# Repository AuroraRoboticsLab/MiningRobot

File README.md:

# UAF Robot Control Architecture, 2023 Version
## Codebase
The autonomy/ directory contains our robot control stack, written in C++ for Linux and running happily on x86 and ARM based robots including the Raspberry Pi or NVIDIA Jetson.  See [the README in that directory](https://github.com/AuroraRoboticsLab/MiningRobot/blob/master/autonomy/README.txt) for build directions.

## LUNATIC
The "Logically UNcoupled Architecture Technology for Intra-robot Communication" or LUNATIC (pronounced lun-AT-ic, like automatic) is our robot control system, built as a loosely coupled set of microservices.

Using microservices means you can compile, run, and test a single service independently, unlike our previous single monolithic executable the [backend](autonomy/backend/main.cpp).  

Due to the nature of a robotics control stack, being able to efficiently exchange quickly changing data between modules is crucial. We do this using the new MMAP-based shared file data exchange system, the details of which can be found in the [data_exchange.h](autonomy/include/aurora/data_exchange.h) header. 

The data being exchanged is listed in the [lunatic.h](autonomy/include/aurora/lunatic.h) header for the microservices, and [nanoslot_exchange.h](autonomy/nanoslot/include/nanoslot/nanoslot_exchange.h) for the Arduino data.

## Control Software Stack
A basic manual control setup has autonomy/frontend running on the "pilot" machine, and sending commands to the autonomy/backend running onboard the robot.  These commands are sent via UDP broadcast, so they should work anywhere on the same subnet.  The backend talks to the Arduinos directly via USB--each Arduino has a "nanoslot ID" that lets nanoboot connect the appropriate slot program to communicate with it.  To control the robot, all you need is a backend and the slot programs: put the backend into "backend driver" state, and use WASD to drive the robot.

For autonomous robot operations, we rely on a huge variety of microservices, such as the localizer (where is the robot?), path planner (how do we get to the target?), andretti (how do we drive along the path?), vision (what obstacles can we see?), and several other debug tools.

This architecture has been incrementally built up since 2013 by a variety of UAF students for the NASA Robotic Mining Contest.  Unless otherwise noted, everything here is public domain. 

For details on how build and run this software, see autonomy/README.
Send a pull request or email lawlor@alaska.edu if you have comments or suggestions!

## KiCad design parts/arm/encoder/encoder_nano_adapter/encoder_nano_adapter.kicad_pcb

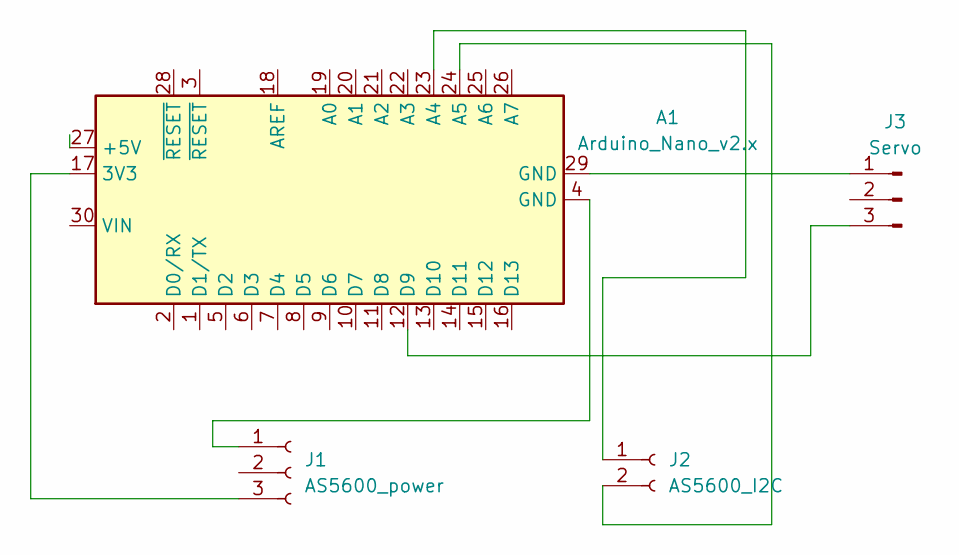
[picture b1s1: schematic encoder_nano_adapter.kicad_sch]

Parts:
A1: Arduino_Nano_v2.x; Arduino_Nano
J1: AS5600_power; PinSocket_1x03_P2.54mm_Vertical
J2: AS5600_I2C; PinSocket_1x02_P2.54mm_Vertical
J3: Servo; PinHeader_1x03_P2.54mm_Vertical

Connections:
unnamed: A1.17 (3V3), J1.3
unnamed: A1.23 (A4), J2.1
unnamed: A1.24 (A5), J2.2
unnamed: A1.12 (D9), J3.3
unnamed: A1.4 (GND), J1.1
unnamed: A1.29 (GND), J3.1

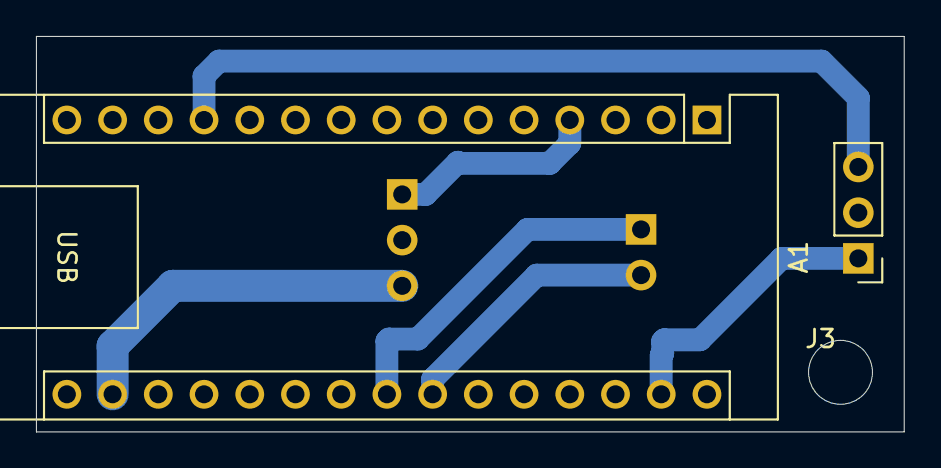
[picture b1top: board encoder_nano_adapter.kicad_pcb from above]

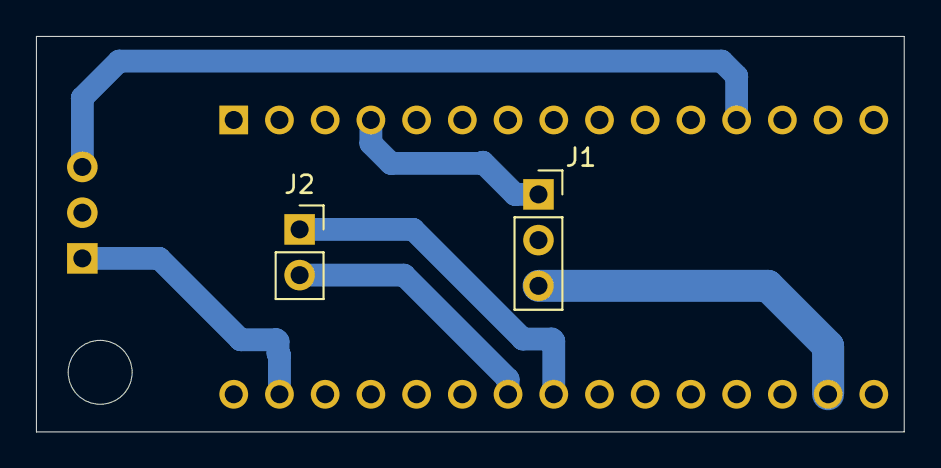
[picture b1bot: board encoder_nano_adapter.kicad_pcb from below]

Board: 2 copper layers, 48.2 x 22.0 mm, 4 parts (2 on the bottom side), 6 nets.

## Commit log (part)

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2023-12-15 Added "--tabletop" vision option, to show simple demo of depth camera processing without a full robot running.
2024-02-22 Moved collision detection constants/functions to excahaul_collision.h
2024-07-29 Swap front scoop controls to match heavy equipment, and sim.
2024-07-29 Don't stop robot because a hazard is detected (e.g., false positive with no tool attached)
2024-09-06 Initial "LawlorBus" test code. Basically like I2C, but instead of pull-up resistors, uses hard I/O pin levels. Designed for direct no-transceiver comms between microcontrollers. Limited to fixed-size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
2024-09-09 Initial 3D printable prototype flat truss.
2024-09-12 Added L truss, with diagonals.
2024-09-23 Add fully 3D printable full-size truss--most vertexes have been printed and tested OK.
2024-09-26 Origami-style truss. Print flat and fold up, to understand geometry.
2024-09-26 Final as-built rev2 trusses, including CAM template for stainless steel endplates.
2024-10-06 These parts used to test geometry of origami truss, mixed results...
2024-10-09 Small demo model of unfolding truss, basically designed as an L truss that can be shipped pre-assembled to the previous truss.
2024-10-28 Initial checkin of a possible robot arm's stepped planetary reducer gear (100:1 reduction ratio).
2024-12-12 3D printed prototype proof of concept works, but needs at least one more revision.
2024-12-13 Significant rework to increase gear reduction ratio (currently 1300:1!) and better constrain motions. Work in progress, hasn't even been test printed.
2024-12-15 Initial ROS2 MoveIt integration for lunatic data exchange and Excahauler robot. Work in progress!
2024-12-18 Version v3C, printed and fully operational! Still needs covers, and could probably be simplified.
2024-12-18 v3F: minor updates to allow multiple motor orientations, guide in bearing screws, tighten up ring bearing clearances.
2025-02-10 Working v4 arm actuator. This "lipless" design works, but wears the sun gear under load, so I think I need to switch back to the retaining bearings.
2025-02-10 Restored planetary bearing lips. About to double the gear reduction, with 4 unique planets.
2025-02-11 v6 actuator design: over 2500:1 total gear reduction, with numbered planets.
2025-02-12 Added "stick" to manually drive sun gear using a cordless drill. It works!
2025-02-17 Version 6, with wire guide tube. Next step is encoder sensor bracket / gear cover.
2025-02-19 Add demo Arduino code to talk to the AS5600 encoder chip, and emit servo PWM commands to a brushless motor controller. Send "t500" to move to angle 500 (using raw numeric angle readings).
2025-02-22 Add support for robot arm motions: UI now requires left bumper to be held for joystick input (deadman switch), hit top bumper for arm mode. Currently only supports slot_70 as firmware for arm's actua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
2025-02-22 Checking in latest arm design, including circuit board to attach to AS5600 angle encoder (Kicad 8 and CAM via pcb2gcode)
2025-02-22 Reduce arm power to 40%, it's way too fast right now.
2025-02-25 Minor motor control firmware tuning. Slightly more responsive now.
2025-02-25 Add a #define to choose between Servo.h and delayMicroseconds.
2025-02-28 Switch PWM microseconds to center point for BLHeli_S ESC.
2025-03-06 Stretch the wiretube so you can feed a USB or Anderson through while assembled. Also added mounting screw to nano adapter board.
2025-04-15 Ambidexterous charge port: can plug into the same part when rotated 180 degrees.
2025-04-29 Added 3D printable demo version of L truss, with print-in-place spring end latches. The vertical upright latch is a little weak as printed, but otherwise this seems robust.
2025-04-30 Shift top clips to two locations on outside, to keep from rotating.
2025-05-08 Reworked arm Arduino firmware so all four copies (ID 70 through 73) share almost all code.
2025-05-08 Oops, don't commit slot binaries.
2025-05-08 Swap UI to only move one arm axis at a time (for debugging, motor controllers are very touchy right now).
2025-05-09 Add debug code to print arm joint angles (to check encoder operation).
2025-05-09 Typo on printf format.
2025-07-07 Added a useful link.
2025-09-18 Moved "LawlorBus" example into the proof of concept folder (it's not something we're using operationally right now, and needs some work).
2025-09-26 Added OpenSCAD source code for cycloplanetary gearbox, and metal-rim printable wheel and hub. (Mostly for reference)
2025-11-07 Demonstration CAD for a rack-and-pinion driven by a linear actuator. The idea is to get a large rotation angle, exceeding 180 degrees, in a small space.
2026-01-17 Separate inside and outside mounting bolt descriptions, allowing up to M5 bolts.
2026-01-19 Updated version of cycloplanetary: supports "teeth_*" for gear-shaped teeth, or trimmed (more trapezoidal) sprocket-shaped teeth, via an include with a rather messy hasty interface.
2026-01-21 Added spacers between the offset bearings. This results in much lower friction while running!
2026-01-22 Shrink the handle a bit, so it fits inside the hex axle hole easily.
2026-02-23 Add CNC-friendly tooth shape of 3/16" diameter roller pins.
2026-03-13 Scale model 4-wheel robot frame, to test: - Bobcat style wheels (axles close together) - Gear-driven front arm actuation
    This is the initial prototype, 3D printed and driving, but not yet easy to assemble or maintain.
2026-03-13 Add initial serial-controlled Arduino Uno firmware.
2026-03-14 1/10th scale model snowblower. It works when driven by a drill at high RPM. Needs two 608 bearings press fit into both ends of the housing, then M3 screws to attach them.
2026-03-14 Half as much height on bearing seats on auger, to avoid confining it in its slot.
2026-03-18 Upgrade to 1/4 scale, to match nanomoose.
2026-03-18 Shrink arm to 30mm, for better torque for heavy tool like snowblower.
2026-03-18 Move shared frame geometry out to interface.scad.
2026-03-19 Checking in working Wifi or Serial firmware.
2026-03-19 Add electronics box on top of rear frame.
